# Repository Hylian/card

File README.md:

card
====

My business card. It enumerates as a USB HID gamepad and has capacitive touch buttons. Uses an ATtiny861 and the V-USB library.

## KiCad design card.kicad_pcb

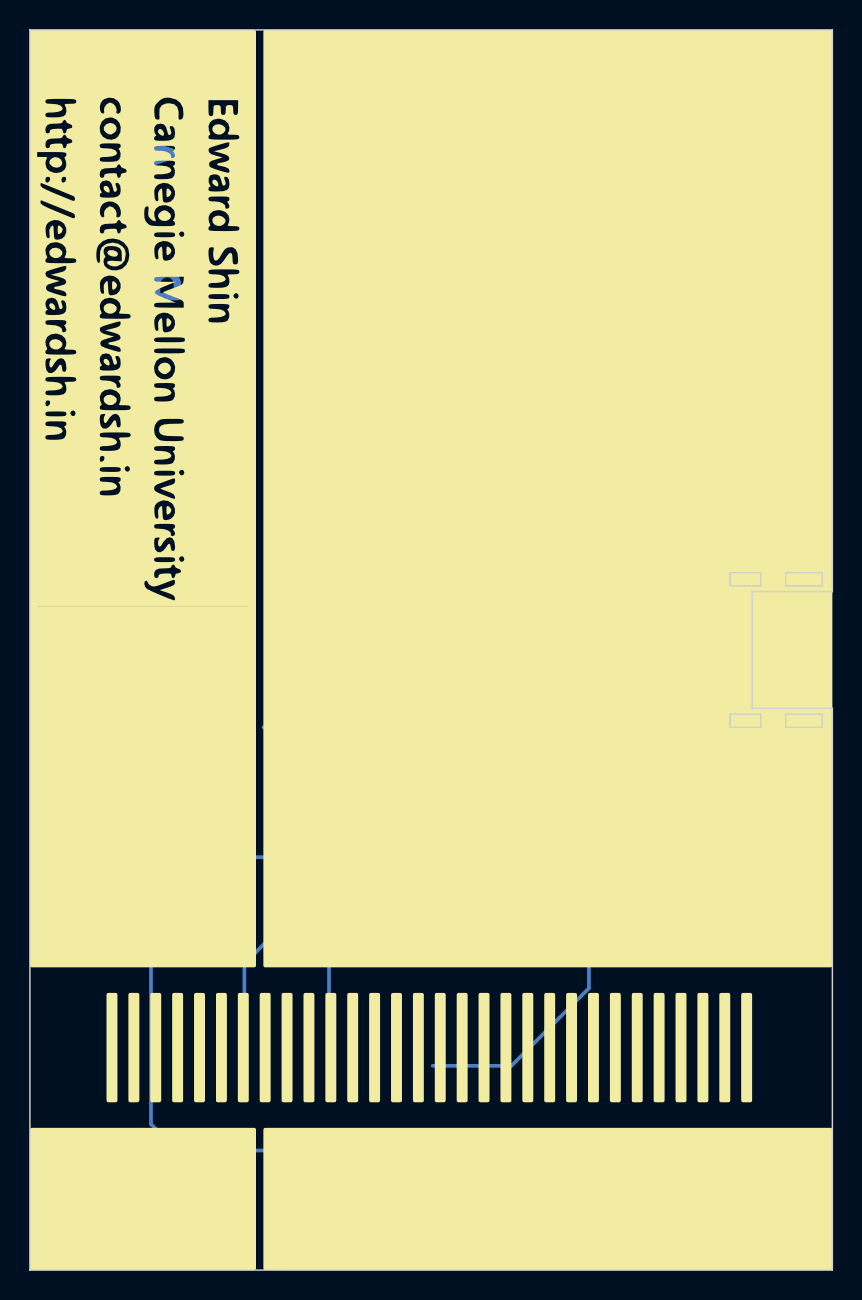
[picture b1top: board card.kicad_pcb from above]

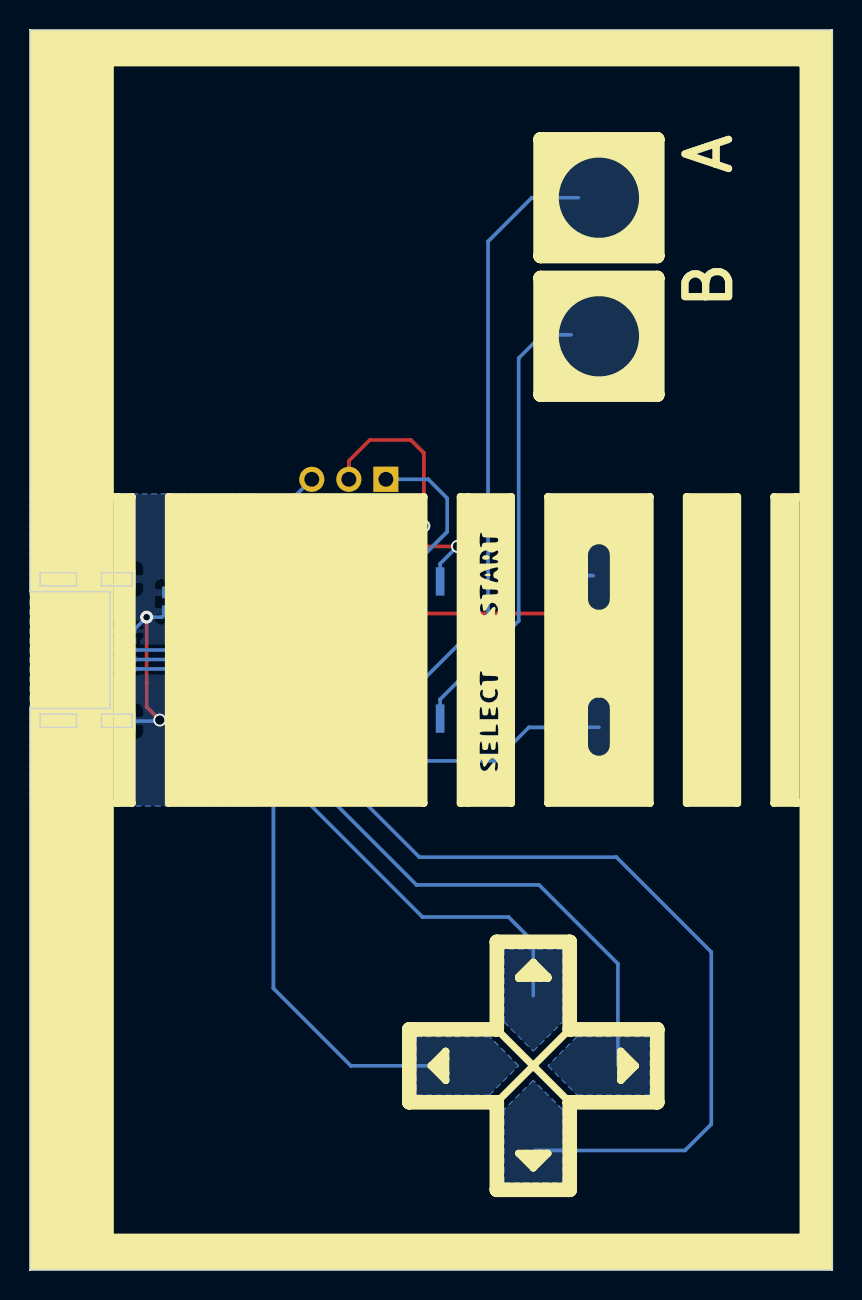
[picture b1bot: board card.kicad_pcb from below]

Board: 2 copper layers, 55.0 x 85.0 mm, 8 parts (8 on the bottom side), 10 nets.

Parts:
C1: 0.1uF; C_0603_HandSoldering
CON1: USB-MINI-B; 15542661MicroUSBB
D1: ZENERARRAY; SMini4-F3-B
IC1: ATTINY26-S; SOIC-20_7.5x12.8mm_Pitch1.27mm
P1: CONN_3X2; Pin_Header_Straight_2x03
R1: 1.5k; R_0603_HandSoldering
R2: 4.7k; R_0603_HandSoldering
RP1: 68R; MNR12

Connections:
+5V: C1.1, CON1.1, IC1.5, IC1.15, P1.2, R1.1, R2.1
/MISO: IC1.2, P1.1
/MOSI: IC1.1, P1.4
/RST: IC1.10, P1.5, R2.2
/SCK: IC1.3, P1.3
GND: C1.2, CON1.5, CON1.6, CON1.7, CON1.8, CON1.9, D1.1, D1.2, IC1.6, IC1.16, P1.6
unnamed: CON1.2, D1.3, R1.2, RP1.4
unnamed: CON1.3, D1.4, RP1.3
unnamed: IC1.8, RP1.1
unnamed: IC1.9, RP1.2

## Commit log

2014-10-20 Before commit to fab.
2015-09-12 rev C to fab
2016-06-09 working attiny26 rev sent to oshpark
2016-08-20 v3, updated with exposed capacitive pads
2016-08-20 move pcb files to subdir
2016-08-20 add firmware files
2016-08-20 modify for attiny861
2016-08-20 fix pcb dir
2016-08-20 added readme description
